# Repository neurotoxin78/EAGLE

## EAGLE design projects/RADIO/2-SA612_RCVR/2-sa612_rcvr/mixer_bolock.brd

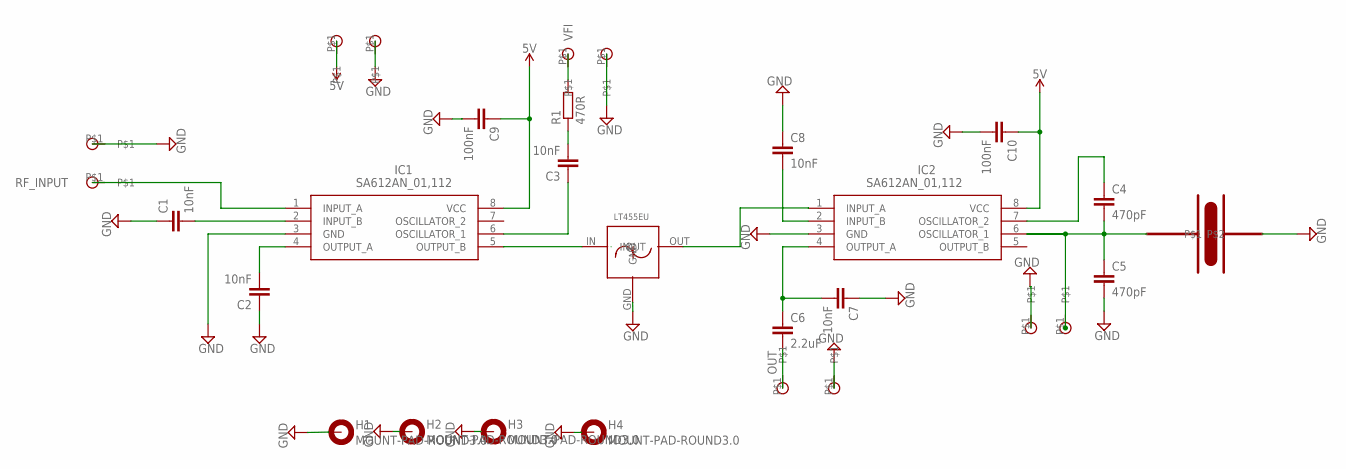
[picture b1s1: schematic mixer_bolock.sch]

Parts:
+5: SMD_PIN
BFI: SMD_PIN
C1, C2, C3, C7, C8: 10nF; C0805K
C4, C5: 470pF; C0805K
C6: 2.2uF; C050-050X075
C9, C10: 100nF; C0805K
H1, H2, H3, H4: MOUNT-PAD-ROUND3.0; 3,0-PAD
IC1, IC2: SA612AN_01,112; DIP762W53P254L950H420Q8N
IN: SMD_PIN
OUT: SMD_PIN
R1: 470R; R0805
U$1: ZTBF455E
U$2, U$4, U$5, U$6, U$7: SMD_PIN
U$9: LT455EU
VFI: SMD_PIN

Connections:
5V: +5.P$1, C9.1, C10.1, IC1.8 (VCC), IC2.8 (VCC)
BFI: BFI.P$1, C4.2, C5.1, IC2.6 (OSCILLATOR_1), U$1.P$1
GND: C1.1, C2.1, C5.2, C7.1, C8.1, C9.2, C10.2, H1.B3,0, H2.B3,0, H3.B3,0, H4.B3,0, IC1.3 (GND), IC2.3 (GND), U$1.P$2, U$2.P$1, U$4.P$1, U$5.P$1, U$6.P$1, U$7.P$1, U$9.GND
unnamed: C1.2, IC1.2 (INPUT_B)
unnamed: IC2.1 (INPUT_A), U$9.OUT
unnamed: C2.2, IC1.4 (OUTPUT_A)
unnamed: C3.2, R1.1
unnamed: C3.1, IC1.6 (OSCILLATOR_1)
unnamed: C4.1, IC2.7 (OSCILLATOR_2)
unnamed: C6.1, C7.2, IC2.4 (OUTPUT_A)
unnamed: C8.2, IC2.2 (INPUT_B)
unnamed: IC1.5 (OUTPUT_B), U$9.IN
OUT: C6.2, OUT.P$1
RF_INPUT: IC1.1 (INPUT_A), IN.P$1
VFI: R1.2, VFI.P$1

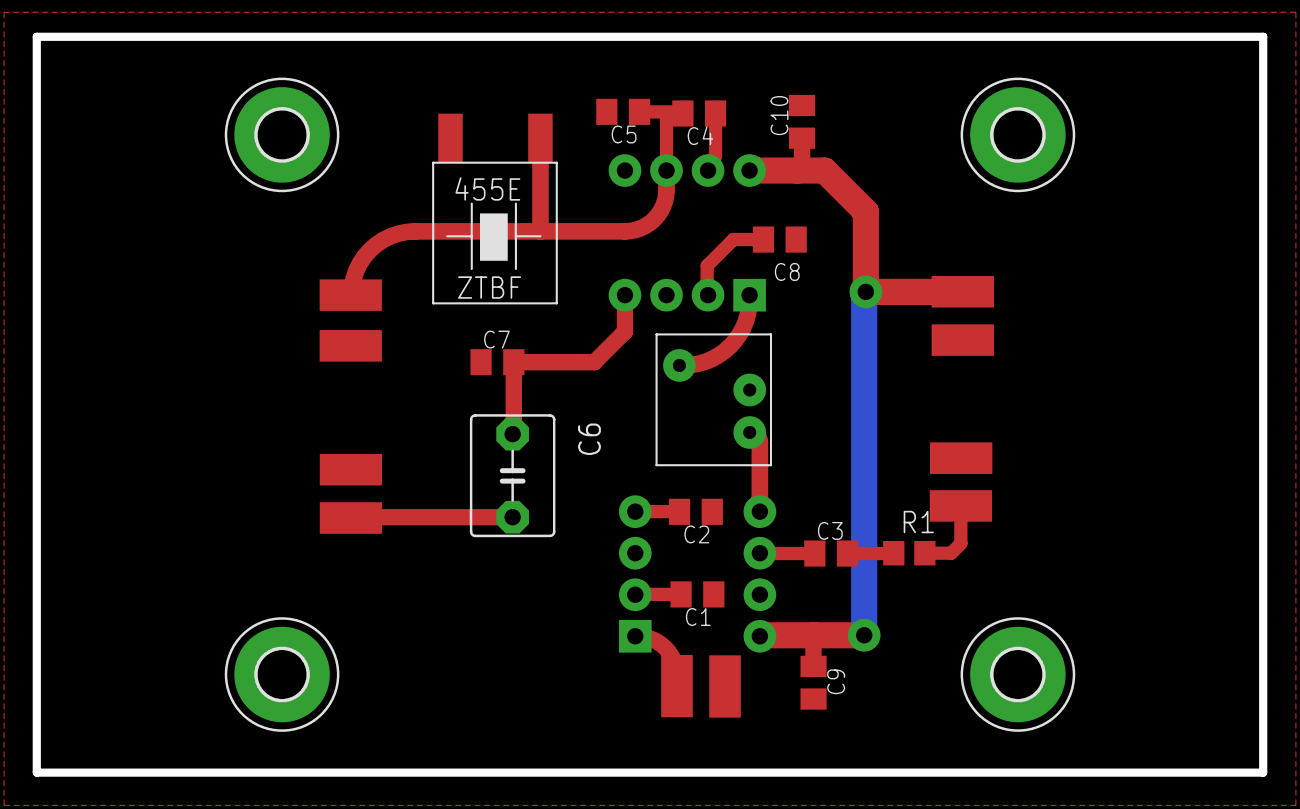
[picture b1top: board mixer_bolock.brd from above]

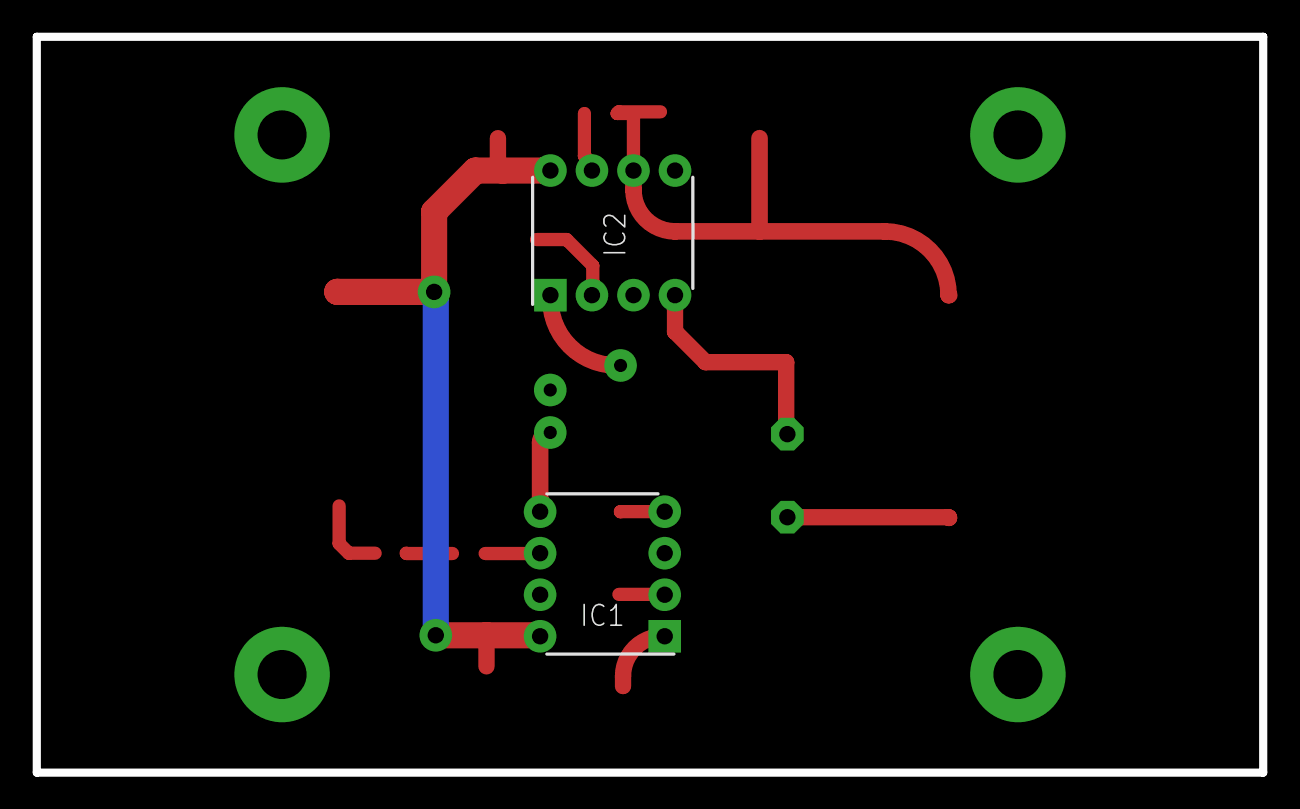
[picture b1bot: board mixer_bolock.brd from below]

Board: 2 copper layers, 75.0 x 45.0 mm, 29 parts (2 on the bottom side), 15 nets.

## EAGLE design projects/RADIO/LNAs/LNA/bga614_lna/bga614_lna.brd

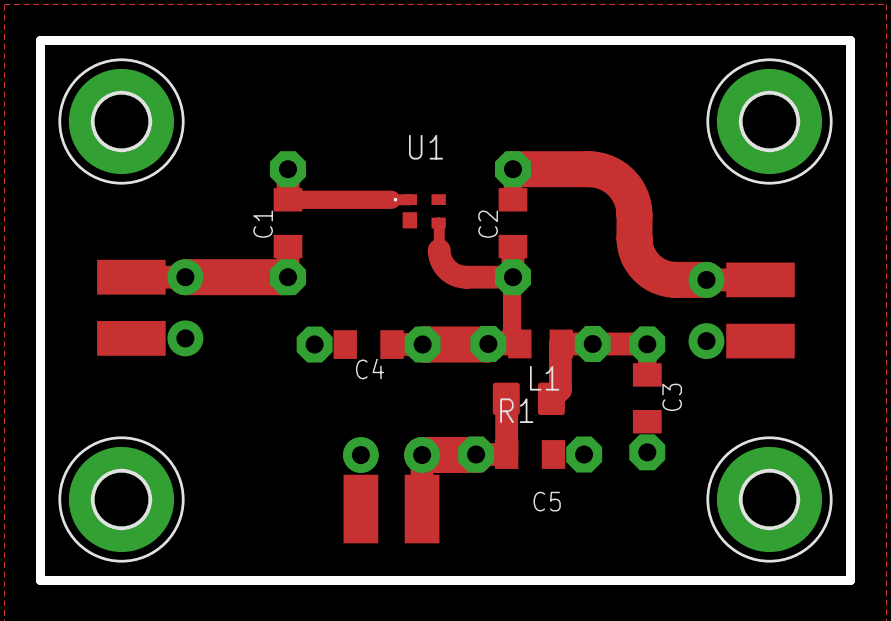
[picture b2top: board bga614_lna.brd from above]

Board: 2 copper layers, 45.0 x 30.0 mm, 15 parts (0 on the bottom side), 7 nets.

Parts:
C1, C2, C3, C4, C5: 10nF; C0805K
H1, H2, H3, H4: MOUNT-PAD-ROUND3.0; 3,0-PAD
L1: 270nH; M0805
PWR: 2X_SMD_PTH_PIN; 2X_SMD_PTH
R1: 68; R0805W
RF_IN: 2X_SMD_PTH_PIN; 2X_SMD_PTH
RF_OUT: 2X_SMD_PTH_PIN; 2X_SMD_PTH
U1: BGA614H6327XTSA1

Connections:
GND: C3.2, C3.P$2, C4.2, C4.P$2, C5.2, C5.P$2, H1.B3,0, H2.B3,0, H3.B3,0, H4.B3,0, PWR.P$1, PWR.T$1, RF_IN.P$2, RF_IN.T$2, RF_OUT.P$1, RF_OUT.T$1, U1.2, U1.4
unnamed: C2.1, C2.P$1, C4.1, C4.P$1, L1.2, L1.P$2, U1.3
unnamed: C3.1, C3.P$1, L1.1, L1.P$1, R1.1
unnamed: C5.1, C5.P$1, PWR.P$2, PWR.T$2, R1.2
unnamed: C2.2, C2.P$2, RF_OUT.P$2, RF_OUT.T$2
unnamed: C1.2, C1.P$2, U1.1
unnamed: C1.1, C1.P$1, RF_IN.P$1, RF_IN.T$1

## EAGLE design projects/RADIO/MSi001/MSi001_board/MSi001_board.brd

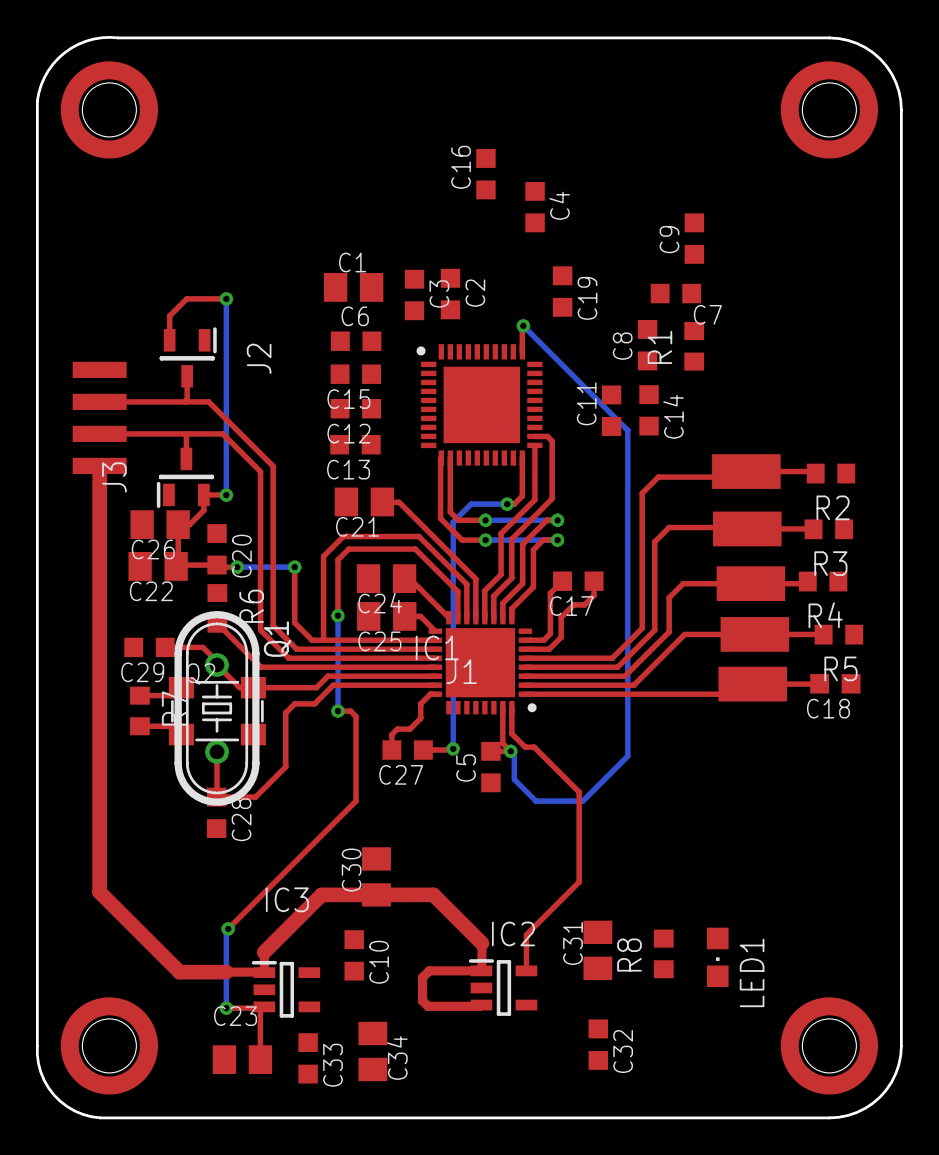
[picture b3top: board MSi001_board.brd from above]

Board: 2 copper layers, 48.0 x 60.0 mm, 61 parts (0 on the bottom side), 42 nets.

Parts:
C1, C24, C25, C26: 1uF; C0805K
C2, C3: 100nF; C0603K
C4, C5, C6, C9, C10, C11, C12, C13, C14, C15, C16, C17, C18, C19, C20, C27, C32, C33: 10nF; C0603K
C7: 6800pF; C0603K
C8: 33nF; C0603K
C21, C22, C23, C30, C31, C34: 10uF; C0805K
C28, C29: 18pF; C0603K
IC1: MSI001; QFN50P600X600X90-41N
IC2: LP2985-33; SOT95P280X145-5N
IC3: LP2985-28; SOT95P280X145-5N
J1: MSI2500; QFN50P500X500X90-33N
J2, J3: BAV99-G; SOT97P230X110-3N
JP1: USB_SOLDER_PADS; USB-SOLDER-PADS
LED1: CHIPLED_0805
Q1: 24MHz; HC49/S
Q2: 5.0X3.2_KXO-83-TCXO
R1: 390R; R0603
R2, R3, R4, R5, R7, R8: 10k; R0603
R6: 510R; R0603
U$1, U$6, U$7, U$8: 3MM_HOLE
U$2, U$3, U$4, U$5: SMD_PIN
VCC_GPIO: SMD_PIN

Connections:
GND: C1.1, C3.1, C4.1, C5.1, C6.1, C9.2, C10.1, C11.2, C12.2, C13.2, C14.1, C15.2, C16.2, C18.1, C19.1, C20.1, C21.2, C22.2, C23.2, C24.2, C25.2, C26.2, C28.2, C29.2, C30.2, C31.2, C32.2, C33.2, C34.2, IC1.41, IC2.2, IC3.2, J1.8, J1.28, J1.29, J1.30, J1.33, J2.1, J3.1, JP1.GND, LED1.C, Q2.2, R2.1, R3.1, R4.1, R5.1, R6.1
I_IN_N: IC1.12, J1.10
I_IN_P: IC1.11, J1.9
unnamed: C2.2, IC1.39
unnamed: C3.2, IC1.40
unnamed: C7.1, C9.1, IC1.28, R1.2
unnamed: C8.1, IC1.26, R1.1
unnamed: C7.2, C8.2, IC1.27
unnamed: C12.1, IC1.7
unnamed: C13.1, IC1.9
unnamed: C15.1, IC1.4
unnamed: C17.2, J1.7
unnamed: C17.1, J1.6
unnamed: C18.2, J1.1, VCC_GPIO.P$1
unnamed: J1.2, R5.2, U$2.P$1
unnamed: J1.3, R4.2, U$3.P$1
unnamed: J1.4, R3.2, U$4.P$1
unnamed: J1.5, R2.2, U$5.P$1
unnamed: C21.1, J1.13
unnamed: C24.1, J1.16
unnamed: C25.1, J1.17
unnamed: J1.21, R6.2
unnamed: C27.2, J1.24
unnamed: C29.1, J1.22, Q1.1, Q2.3
unnamed: C28.1, J1.23, Q1.2
unnamed: LED1.A, R8.2
unnamed: Q2.1, R7.2
unnamed: C30.1, IC2.1, IC2.3, IC3.1, JP1.VBUS
unnamed: C33.1, IC3.4
unnamed: C32.1, IC2.4
Q_IN_N: IC1.21, J1.12
Q_IN_P: IC1.22, J1.11
REFCLK: C27.1, IC1.20
SPI_CLK: IC1.34, J1.27
SPI_DATA: IC1.35, J1.26
SPI_LAT: IC1.33, J1.25
USB_DM: J1.20, J3.3, JP1.D-
USB_DP: J1.19, J2.3, JP1.D+
V18-SYNTH: C23.1, IC3.3, J1.15
VDDI: C5.2, C19.2, IC1.31, J1.31
VDIG: C20.2, C22.1, C26.1, C31.1, IC2.5, J1.14, J1.18, J1.32, J2.2, J3.2, Q2.4, R7.1, R8.1
VRF: C1.2, C4.2, C6.2, C10.2, C11.1, C14.2, C16.1, C34.1, IC1.1, IC1.2, IC1.8, IC1.14, IC1.15, IC1.18, IC1.19, IC1.23, IC1.29, IC1.30, IC1.32, IC1.36, IC3.5

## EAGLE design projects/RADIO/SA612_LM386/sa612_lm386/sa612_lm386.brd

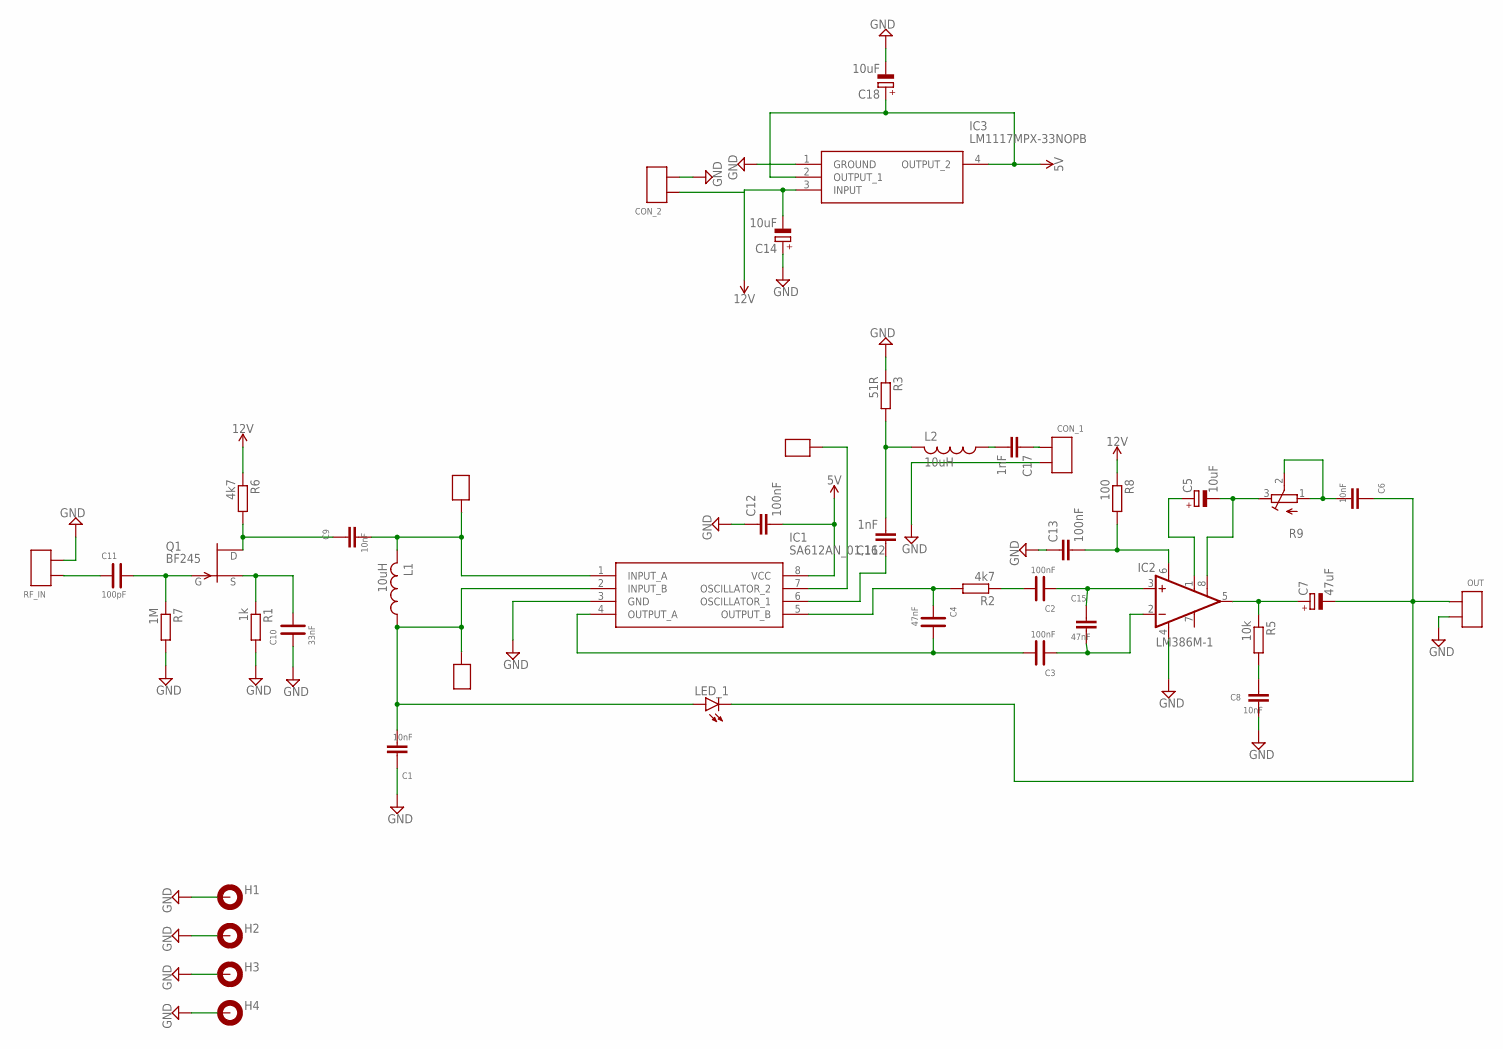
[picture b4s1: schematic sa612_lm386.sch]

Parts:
C1, C6, C8, C9: 10nF; C0805
C2, C3: 100nF; C0805K
C4: 47nF; C0805K
C5, C14, C18: 10uF; E5-5
C7: 47uF; E5-5
C10: 33nF; C0805K
C11: 100pF; C0805K
C12, C13: 100nF; C0805
C15: 47nF; C0805
C16, C17: 1nF; C0805
CON_1, CON_2: 2X_SMD_PTH_PIN; 2X_SMD_PTH
H1, H2, H3, H4: MOUNT-PAD-ROUND3.0; 3,0-PAD
IC1: SA612AN_01,112; DIP762W53P254L950H420Q8N
IC2: LM386M-1; SO08
IC3: LM1117MPX-33NOPB; SOT230P700X180-4N
IN_A: SMD_PIN
IN_B: SMD_PIN
L1, L2: 10uH; M0805
LED_1: LED_0805_PTH; CHIP-LED0805
OUT: 2X_SMD_PTH_PIN; 2X_SMD_PTH
P_1: SMD_PIN
Q1: BF245; TO92
R1: 1k; R0805
R2: 4k7; R0805W
R3: 51R; R0805W
R5: 10k; R0805W
R6: 4k7; R0805
R7: 1M; R0805
R8: 100; R0805W
R9: R-TRIMM64W; RTRIM64W
RF_IN: 2X_SMD_PTH_PIN; 2X_SMD_PTH

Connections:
5V: C12.2, C18.+, IC1.8 (VCC), IC3.2 (OUTPUT_1), IC3.4 (OUTPUT_2)
12V: C14.-, CON_2.P$1 (PIN0), CON_2.T$1 (PIN0), IC3.3 (INPUT), R6.1, R6.P$1 (1), R8.1
GND: C1.1, C8.2, C10.1, C10.P$1 (1), C12.1, C13.1, C14.+, C18.-, CON_1.P$2 (PIN1), CON_1.T$2 (PIN1), CON_2.P$2 (PIN1), CON_2.T$2 (PIN1), H1.B3,0, H2.B3,0, H3.B3,0, H4.B3,0, IC1.3 (GND), IC2.4 (GND), IC3.1 (GROUND), OUT.P$2 (PIN1), OUT.T$2 (PIN1), R1.2, R1.P$2 (2), R3.1, R7.2, R7.P$2 (2), RF_IN.P$2 (PIN1), RF_IN.T$2 (PIN1)
unnamed: C9.2, IC1.1 (INPUT_A), IN_A.P$1, L1.2, L1.P$2 (2)
unnamed: C1.2, IC1.2 (INPUT_B), IN_B.P$1, L1.1, L1.P$1 (1), LED_1.A, LED_1.AP (A)
unnamed: C2.1, C2.P$1 (1), C15.1, IC2.3 (+IN)
unnamed: C3.1, C3.P$1 (1), C15.2, IC2.2 (-IN)
unnamed: C16.2, L2.2, L2.P$2 (2), R3.2
unnamed: C2.2, C2.P$2 (2), R2.1
unnamed: C4.1, C4.P$1 (1), IC1.5 (OUTPUT_B), R2.2
unnamed: C3.2, C3.P$2 (2), C4.2, C4.P$2 (2), IC1.4 (OUTPUT_A)
unnamed: C16.1, IC1.6 (OSCILLATOR_1)
unnamed: IC1.7 (OSCILLATOR_2), P_1.P$1
unnamed: C5.+, IC2.1 (GAIN)
unnamed: C5.-, IC2.8 (GAIN), R9.3 (E)
unnamed: C6.2, R9.1 (A), R9.2 (S)
unnamed: C6.1, C7.-, LED_1.C, LED_1.CP (C), OUT.P$1 (PIN0), OUT.T$1 (PIN0)
unnamed: C7.+, IC2.5 (OUT), R5.1
unnamed: C8.1, R5.2
unnamed: C10.2, C10.P$2 (2), Q1.2 (S), R1.1, R1.P$1 (1)
unnamed: C9.1, Q1.1 (D), R6.2, R6.P$2 (2)
unnamed: C11.2, C11.P$2 (2), Q1.3 (G), R7.1, R7.P$1 (1)
unnamed: C11.1, C11.P$1 (1), RF_IN.P$1 (PIN0), RF_IN.T$1 (PIN0)
unnamed: C13.2, IC2.6 (VS), R8.2
unnamed: C17.1, CON_1.P$1 (PIN0), CON_1.T$1 (PIN0)
unnamed: C17.2, L2.1, L2.P$1 (1)

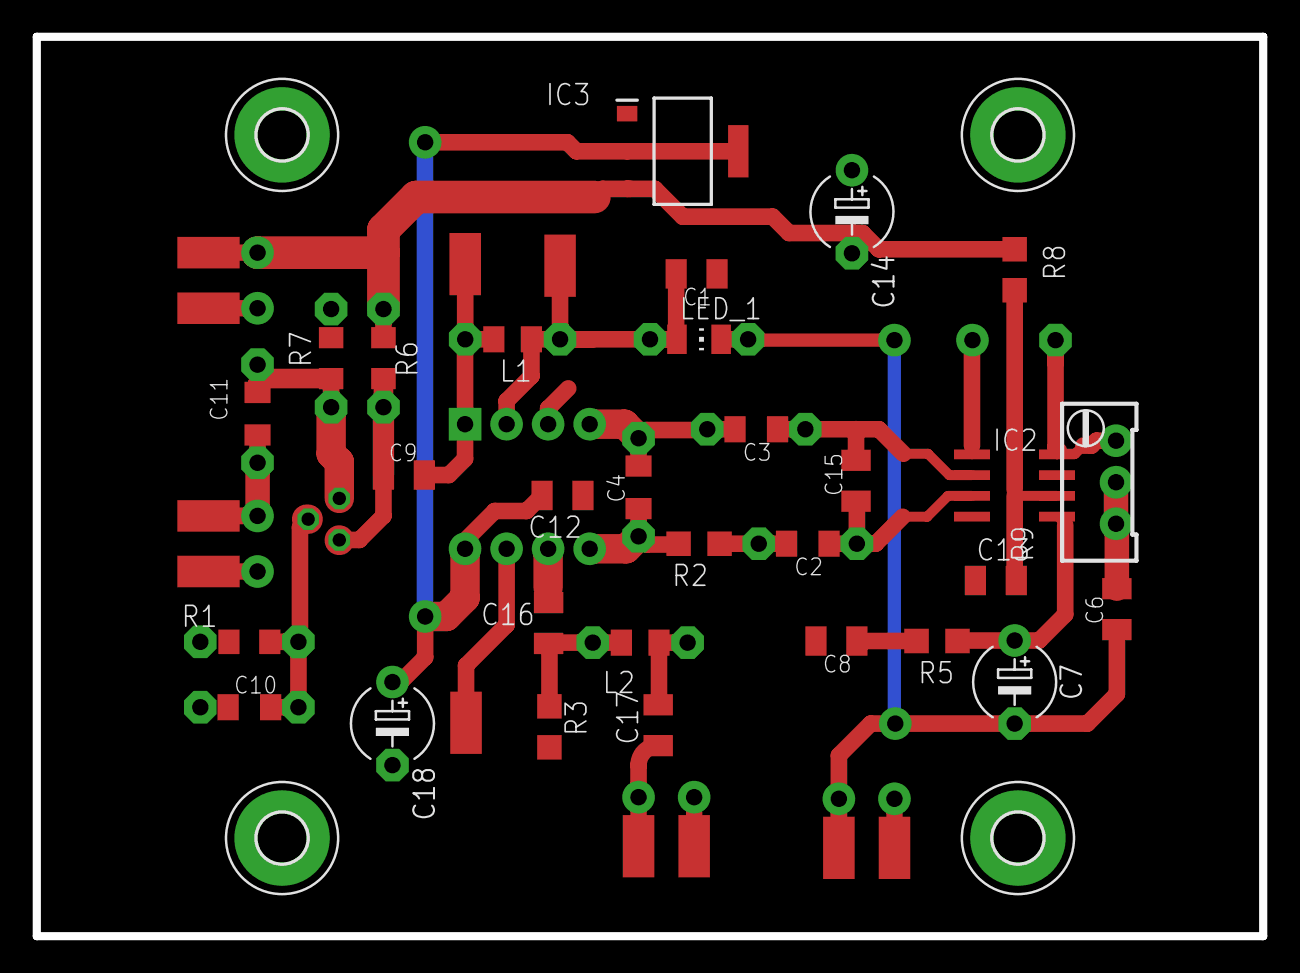
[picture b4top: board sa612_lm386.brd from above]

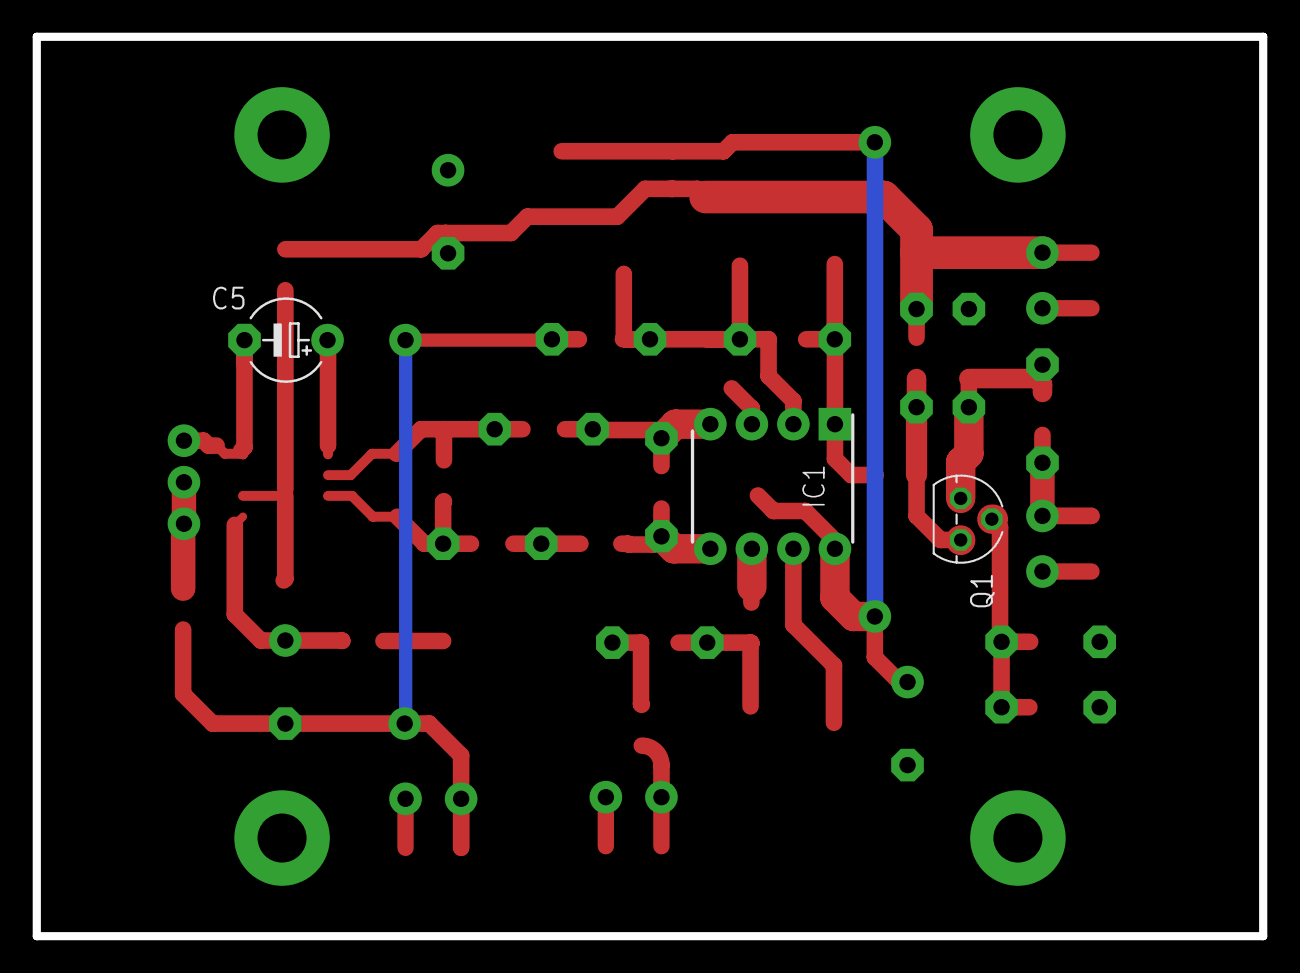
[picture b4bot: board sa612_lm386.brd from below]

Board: 2 copper layers, 75.0 x 55.0 mm, 44 parts (3 on the bottom side), 26 nets.

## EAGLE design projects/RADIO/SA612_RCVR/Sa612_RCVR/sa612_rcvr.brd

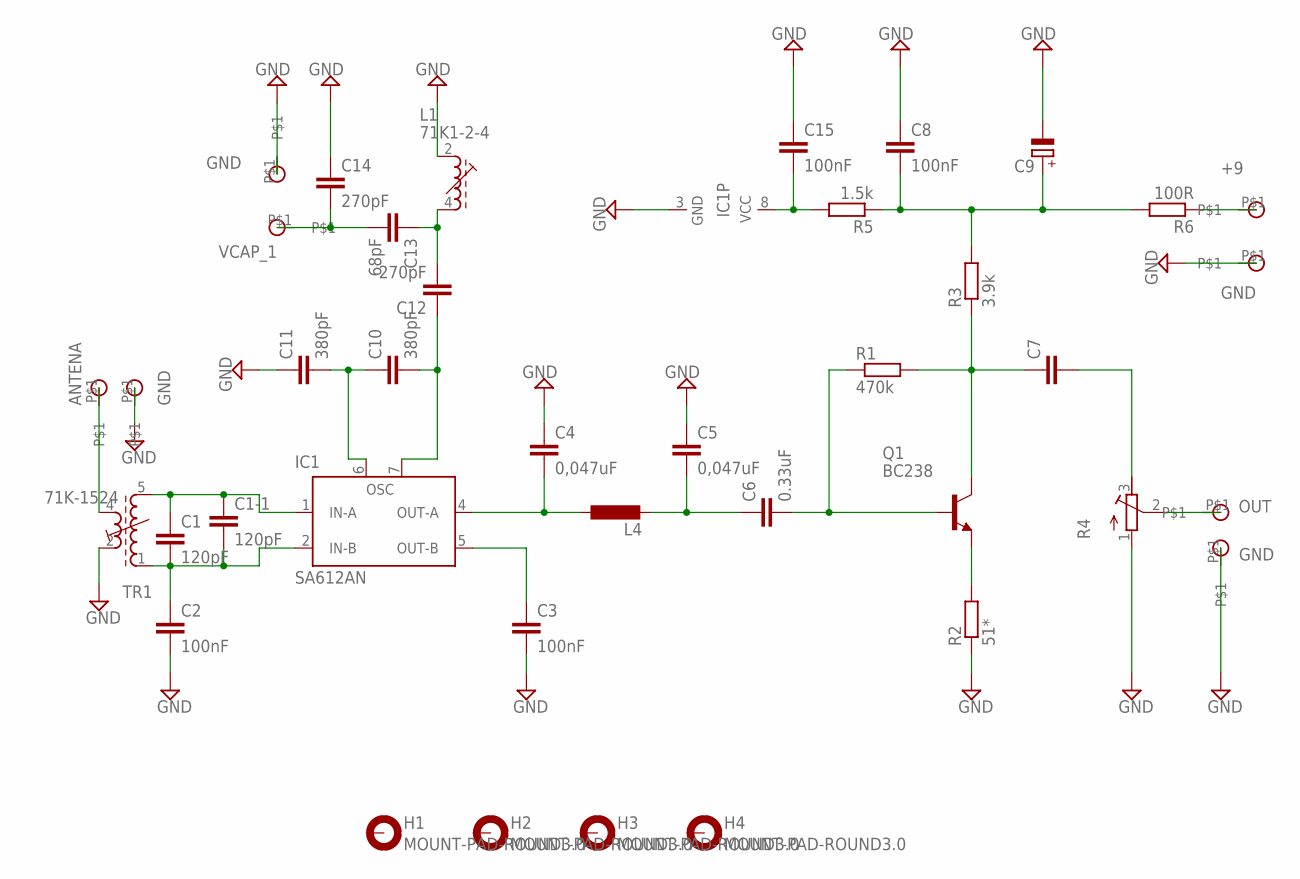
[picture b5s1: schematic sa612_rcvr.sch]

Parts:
C1: 120pF; C0805K
C1-1: 120pF; C050-025X075
C2, C3, C8, C15: 100nF; C0805K
C4, C5: 0,047uF; C0805K
C6: 0.33uF; C0805K
C7: C-EU050-025X075; C050-025X075
C9: CPOL-EUE5-8.5; E5-8,5
C10, C11: 380pF; C0805K
C12, C14: 270pF; C0805K
C13: 68pF; C0805K
H1, H2, H3, H4: MOUNT-PAD-ROUND3.0; 3,0-PAD
IC1: SA612AN; DIL08
L1: 71K1-2-4; 71K
L4: L-EU6000-XXX-RC; 6000-XXXX-RC
Q1: BC238; TO92
R1: 470k; R0805
R2: 51*; R0805
R3: 3.9k; R0805
R4: R-TRIMM64X; RTRIM64X
R5: 1.5k; R0805
R6: 100R; R0805
TR1: 71K-1524; 71K
U$1, U$2, U$3, U$4, U$5, U$6, U$7, U$8: SMD_PIN

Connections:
+9: R6.1, U$5.P$1
ANTENA: TR1.4 (E2), U$3.P$1
GND: C2.2, C3.2, C4.1, C5.1, C8.1, C9.-, C11.1, C14.1, C15.1, IC1.3 (GND), L1.2 (A), R2.1, R4.1 (A), TR1.2 (A2), U$2.P$1, U$4.P$1, U$6.P$1, U$8.P$1
unnamed: C1.1, C1-1.1, IC1.1 (IN-A), TR1.5 (E1)
unnamed: C1.2, C1-1.2, C2.1, IC1.2 (IN-B), TR1.1 (A1)
unnamed: C3.1, IC1.5 (OUT-B)
unnamed: C4.2, IC1.4 (OUT-A), L4.1
unnamed: C5.2, C6.1, L4.2
unnamed: C6.2, Q1.2 (B), R1.1
unnamed: Q1.1 (E), R2.2
unnamed: C7.1, Q1.3 (C), R1.2, R3.1
unnamed: C7.2, R4.3 (E)
unnamed: C15.2, IC1.8 (VCC), R5.2
unnamed: C8.2, C9.+, R3.2, R5.1, R6.2
unnamed: C10.1, C11.2, IC1.6 (OSC)
unnamed: C10.2, C12.1, IC1.7 (OSC')
unnamed: C12.2, C13.1, L1.4 (E)
OUT: R4.2 (S), U$1.P$1
VCAP_1: C13.2, C14.2, U$7.P$1

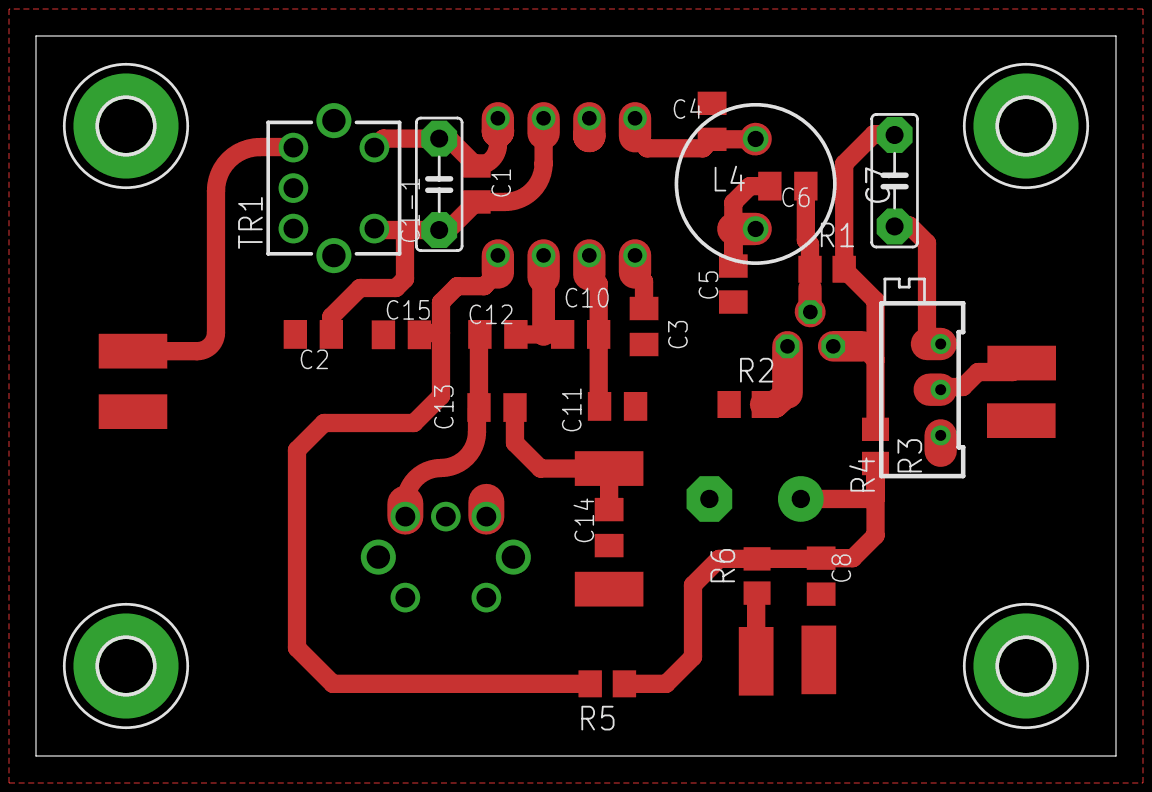
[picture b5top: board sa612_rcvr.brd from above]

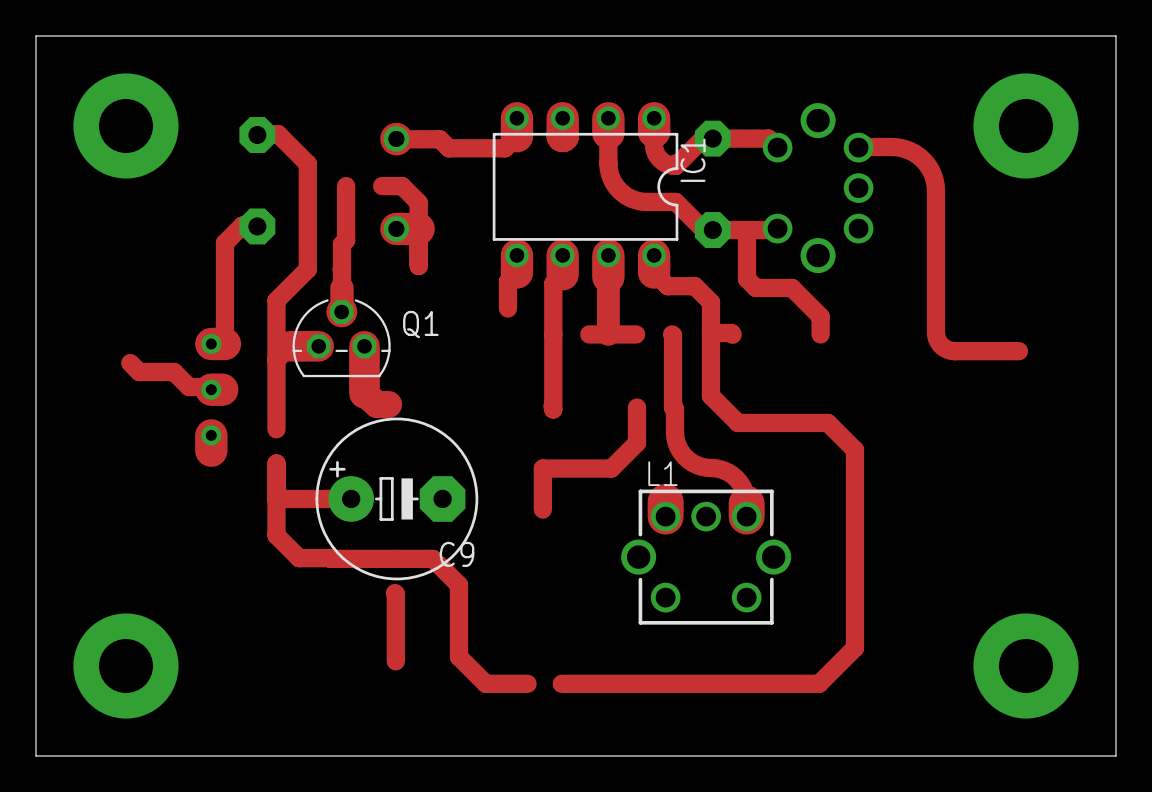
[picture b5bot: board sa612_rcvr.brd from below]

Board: 2 copper layers, 60.0 x 40.0 mm, 39 parts (4 on the bottom side), 19 nets.

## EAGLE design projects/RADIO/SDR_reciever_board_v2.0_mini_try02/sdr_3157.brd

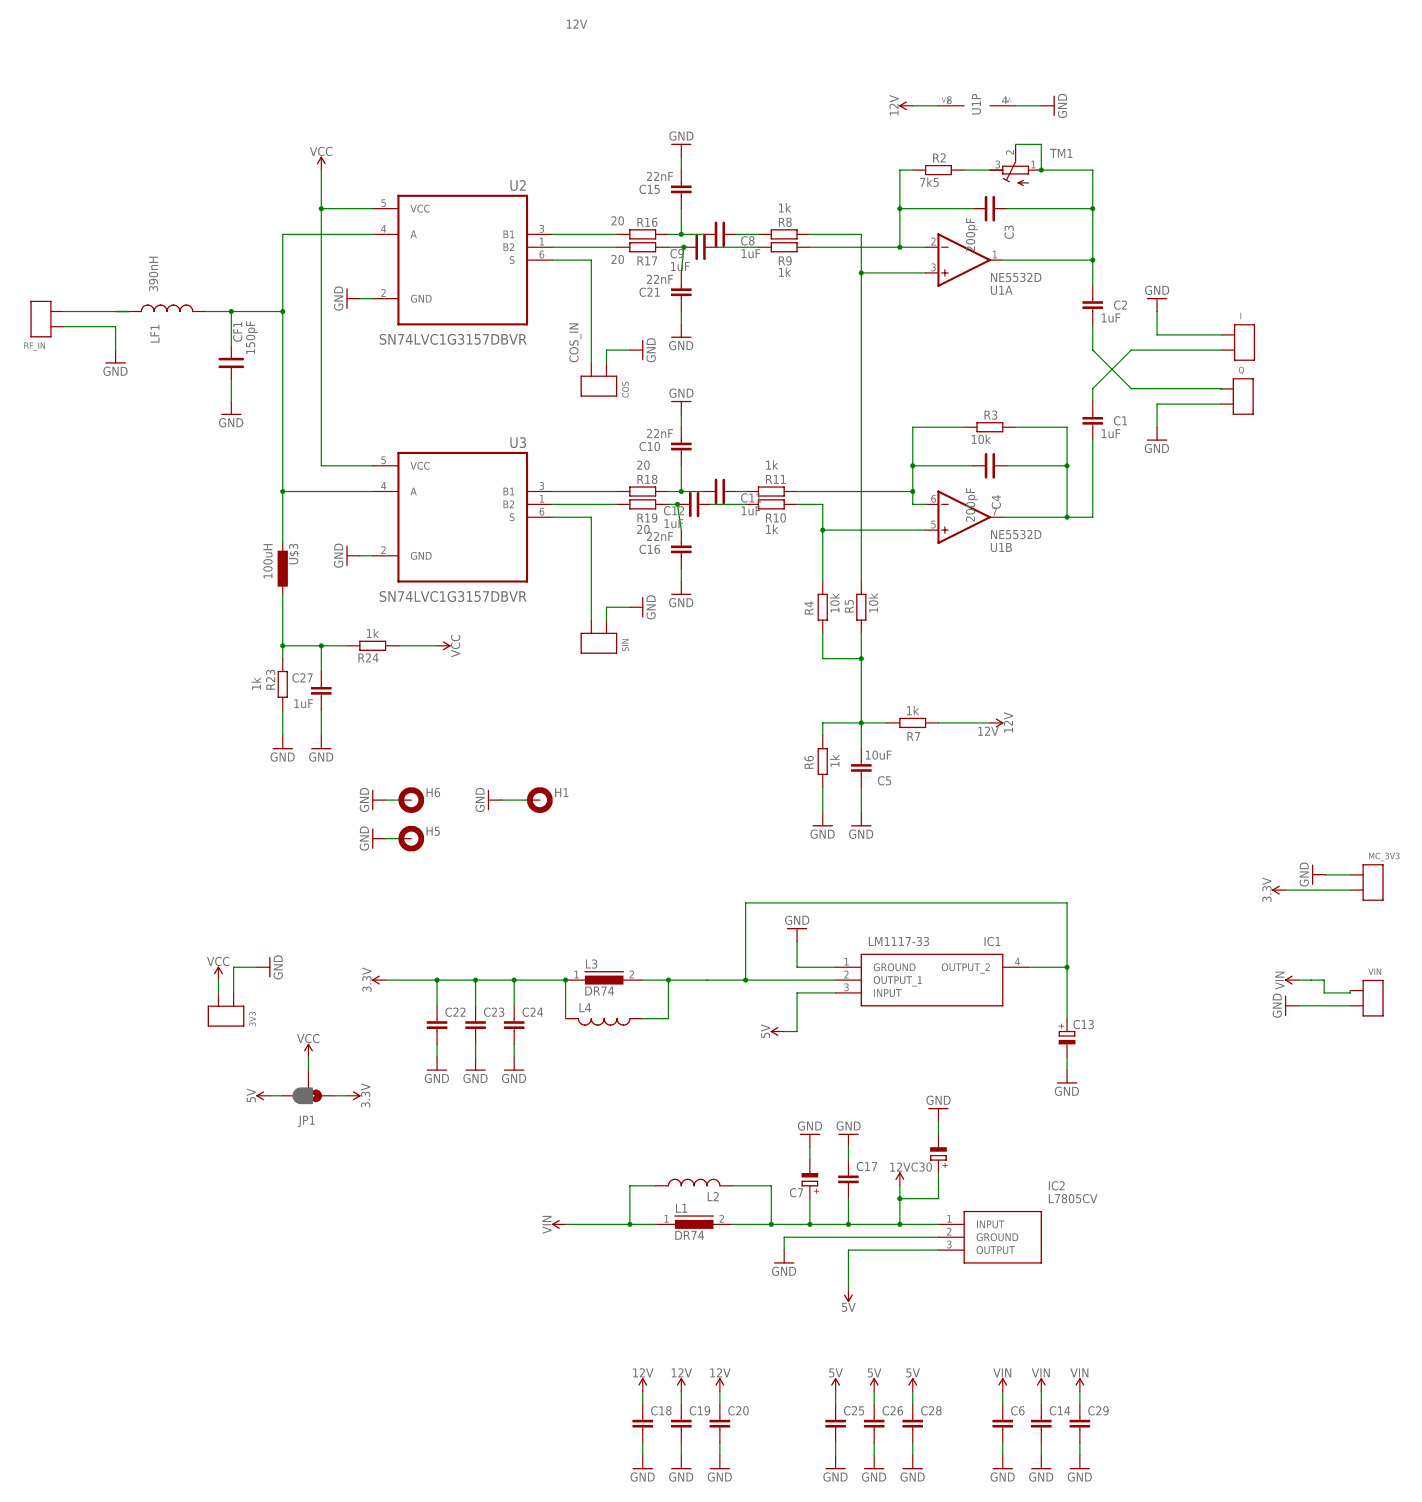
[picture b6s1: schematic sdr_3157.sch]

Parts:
3V3: 2X_SMD_PTH_PIN; 2X_SMD_PTH
C1, C2: 1uF; C050-045X075
C3, C4: 200pF; C0805K
C5: 10uF; C0805
C6, C14, C17, C18, C19, C20, C22, C23, C24, C25, C26, C28, C29: C_0805_SMD; C0805
C7, C13, C30: C_POL; E5-5
C8, C9, C11, C12: 1uF; C0805K
C10, C15, C16, C21: 22nF; C0805
C27: 1uF; C0805
CF1: 150pF; C0805K
COS: 2X_SMD_PTH_PIN; 2X_SMD_PTH
H1, H5, H6: MOUNT-PAD-ROUND3.0; 3,0-PAD
I: 2X_SMD_PTH_PIN; 2X_SMD_PTH
IC1: LM1117-33; SOT230P700X180-4N
IC2: L7805CV; TO255P460X1020X2008-3P
JP1: JUMPER-SMT_3_1-NC_PASTE_NO-SILK; SMT-JUMPER_3_1-NC_PASTE_NO-SILK
L1, L3: DR74
L2, L4: L_0805_PTH; M0805
LF1: 390nH; M0805
MC_3V3: 2X_SMD_PTH_PIN; 2X_SMD_PTH
Q: 2X_SMD_PTH_PIN; 2X_SMD_PTH
R2: 7k5; R0805W
R3, R4, R5: 10k; R0805W
R6, R7, R8, R9, R10, R11, R23, R24: 1k; R0805W
R16, R17, R18, R19: 20; R0805W
RF_IN: 2X_SMD_PTH_PIN; 2X_SMD_PTH
SIN: 2X_SMD_PTH_PIN; 2X_SMD_PTH
TM1: 5k; RTRIM3296W
U1: NE5532D; SO08
U2, U3: SN74LVC1G3157DBVR; SOT95P280X145-6N
U$3: 100uH; 0207/10
VIN: 2X_SMD_PTH_PIN; 2X_SMD_PTH

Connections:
3.3V: C22.1, C23.1, C24.1, JP1.1, L3.1, L4.2, L4.P$2 (2), MC_3V3.P$2 (PIN1), MC_3V3.T$2 (PIN1)
5V: C25.1, C26.1, C28.1, IC1.3 (INPUT), IC2.3 (OUTPUT), JP1.3
12V: C7.+, C17.2, C18.1, C19.1, C20.1, C30.+, IC2.1 (INPUT), L1.2, L2.2, L2.P$2 (2), R7.1, U1.8 (V+)
ANTENNA: CF1.2, CF1.P$2 (2), LF1.2, LF1.P$2 (2), U2.4 (A), U3.4 (A), U$3.2
COS_IN: COS.P$2 (PIN1), COS.T$2 (PIN1), U2.6 (S)
GND: 3V3.P$1 (PIN0), 3V3.T$1 (PIN0), C5.1, C6.2, C7.-, C10.2, C13.-, C14.2, C15.2, C16.1, C17.1, C18.2, C19.2, C20.2, C21.1, C22.2, C23.2, C24.2, C25.2, C26.2, C27.1, C28.2, C29.2, C30.-, CF1.1, CF1.P$1 (1), COS.P$1 (PIN0), COS.T$1 (PIN0), H1.B3,0, H5.B3,0, H6.B3,0, I.P$1 (PIN0), I.T$1 (PIN0), IC1.1 (GROUND), IC2.2 (GROUND), MC_3V3.P$1 (PIN0), MC_3V3.T$1 (PIN0), Q.P$2 (PIN1), Q.T$2 (PIN1), R6.1, R23.1, RF_IN.P$1 (PIN0), RF_IN.T$1 (PIN0), SIN.P$1 (PIN0), SIN.T$1 (PIN0), U1.4 (V-), U2.2 (GND), U3.2 (GND), VIN.P$2 (PIN1), VIN.T$2 (PIN1)
unnamed: LF1.1, LF1.P$1 (1), RF_IN.P$2 (PIN1), RF_IN.T$2 (PIN1)
unnamed: R16.1, U2.3 (B1)
unnamed: R17.1, U2.1 (B2)
unnamed: R18.1, U3.3 (B1)
unnamed: C13.+, IC1.2 (OUTPUT_1), IC1.4 (OUTPUT_2), L3.2, L4.1, L4.P$1 (1)
unnamed: R19.1, U3.1 (B2)
unnamed: C8.1, C8.P$1 (1), C15.1, R16.2
unnamed: C9.1, C9.P$1 (1), C21.2, R17.2
unnamed: C10.1, C11.1, C11.P$1 (1), R18.2
unnamed: C12.1, C12.P$1 (1), C16.2, R19.2
unnamed: C8.2, C8.P$2 (2), R8.1
unnamed: C9.2, C9.P$2 (2), R9.1
unnamed: C11.2, C11.P$2 (2), R11.1
unnamed: C12.2, C12.P$2 (2), R10.1
unnamed: R5.2, R8.2, U1.3 (+IN)
unnamed: C3.1, C3.P$1 (1), R2.1, R9.2, U1.2 (-IN)
unnamed: R4.2, R10.2, U1.5 (+IN)
unnamed: C4.1, C4.P$1 (1), R3.1, R11.2, U1.6 (-IN)
unnamed: C5.2, R4.1, R5.1, R6.2, R7.2
unnamed: C2.1, C3.2, C3.P$2 (2), TM1.1 (A), TM1.2 (S), U1.1 (OUT)
unnamed: C2.2, Q.P$1 (PIN0), Q.T$1 (PIN0)
unnamed: C1.1, I.P$2 (PIN1), I.T$2 (PIN1)
unnamed: C1.2, C4.2, C4.P$2 (2), R3.2, U1.7 (OUT)
unnamed: C27.2, R23.2, R24.2, U$3.1
unnamed: R2.2, TM1.3 (E)
SIN_IN: SIN.P$2 (PIN1), SIN.T$2 (PIN1), U3.6 (S)
VCC: 3V3.P$2 (PIN1), 3V3.T$2 (PIN1), JP1.2, R24.1, U2.5 (VCC), U3.5 (VCC)
VIN: C6.1, C14.1, C29.1, L1.1, L2.1, L2.P$1 (1), VIN.P$1 (PIN0), VIN.T$1 (PIN0)

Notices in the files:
parts and their libraries:
SparkFun-PowerSymbols: Licensing: Creative Commons ShareAlike 4.0 International - https://creativecommons.org/licenses/by-sa/4.0
crystal-geyer_V1_0: Copyright: Geyer-Electronic
op-amp: Copyright (C) 2006 by Bob Starr
